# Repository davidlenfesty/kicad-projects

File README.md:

# kicad-projects

A repo for all my personal kicad PCB projects.

Included are some LED drivers for home automation purposes.

There isn't really anything special about this stuff.

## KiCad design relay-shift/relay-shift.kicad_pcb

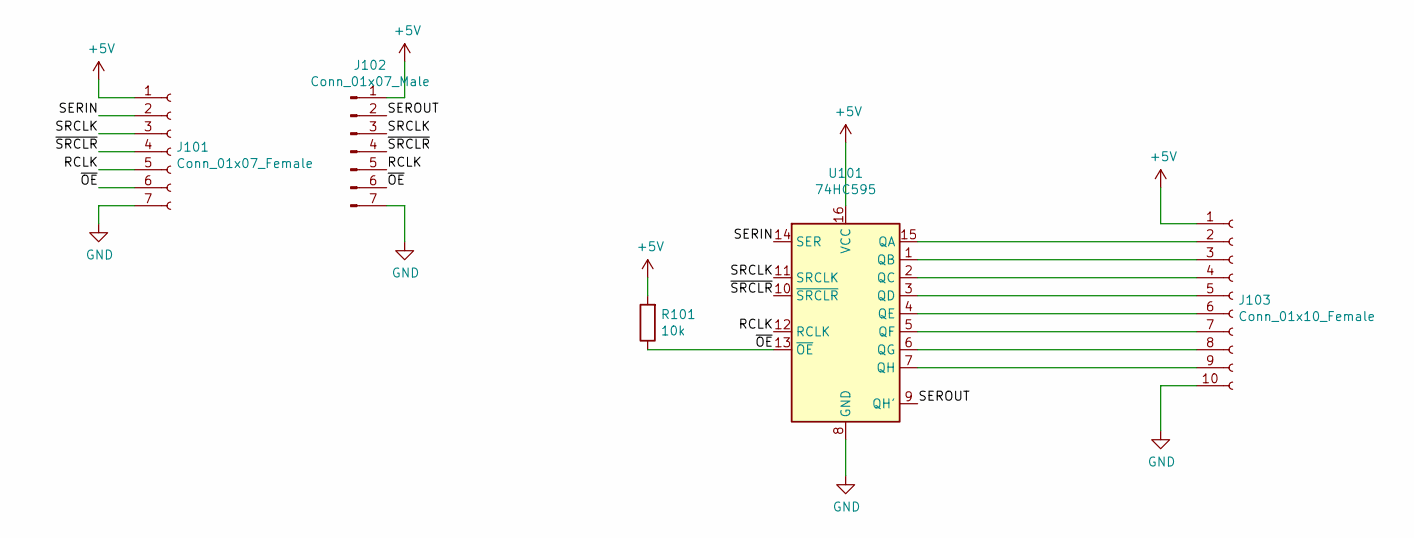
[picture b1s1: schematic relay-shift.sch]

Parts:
J101: Conn_01x07_Female; Molex_CLIK-Mate_502494-0870_1x08-1MP_P2.00mm_Horizontal
J102: Conn_01x07_Male; Molex_CLIK-Mate_502494-0870_1x08-1MP_P2.00mm_Horizontal
J103: Conn_01x10_Female; PinHeader_1x10_P2.54mm_Vertical
R101: 10k; R_0805_2012Metric
U101: 74HC595; SOIC-16W_7.5x10.3mm_P1.27mm

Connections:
+5V: J101.1, J102.1, J103.1, R101.2, U101.16 (VCC)
/RCLK: J101.5, J102.5, U101.12 (RCLK)
/SERIN: J101.2, U101.14 (SER)
/SEROUT: J102.2, U101.9 (QH')
/SRCLK: J101.3, J102.3, U101.11 (SRCLK)
/~OE: J101.6, J102.6, R101.1, U101.13 (~OE)
/~SRCLR: J101.4, J102.4, U101.10 (~SRCLR)
GND: J101.7, J102.7, J103.10, U101.8 (GND)
unnamed: J103.2, U101.15 (QA)
unnamed: J103.3, U101.1 (QB)
unnamed: J103.4, U101.2 (QC)
unnamed: J103.5, U101.3 (QD)
unnamed: J103.6, U101.4 (QE)
unnamed: J103.7, U101.5 (QF)
unnamed: J103.8, U101.6 (QG)
unnamed: J103.9, U101.7 (QH)

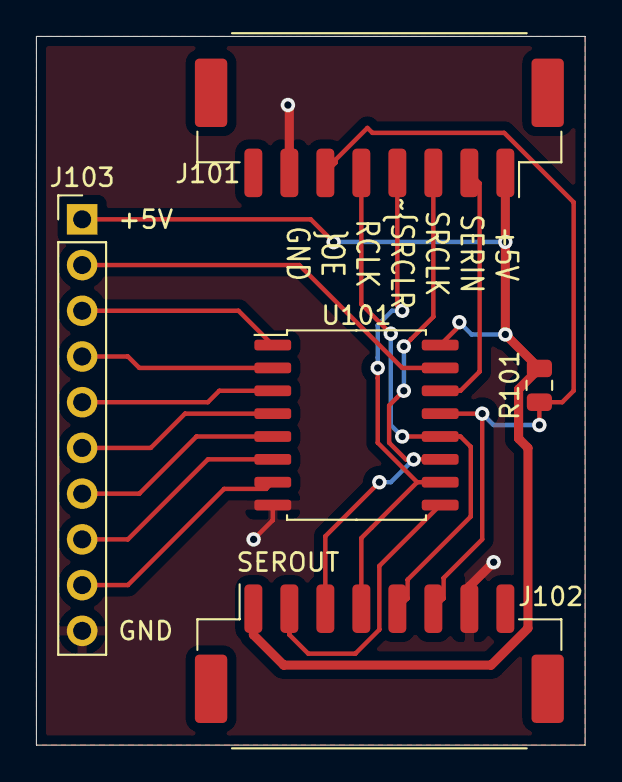
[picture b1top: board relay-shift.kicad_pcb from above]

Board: 2 copper layers, 30.5 x 39.4 mm, 5 parts (0 on the bottom side), 16 nets.

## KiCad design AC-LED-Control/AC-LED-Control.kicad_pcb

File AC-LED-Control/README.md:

# DO NOT USE THIS #

I made this board for a personal project.

Never use this.

I made this board using what I *think* were good tolerances.

Never use this.

I have not had the time to test this board.

Never use this.

This board is designed for AC.

Never use this.

Unless it's like 24VAC then that's okay I guess but I'm not responsible for it.

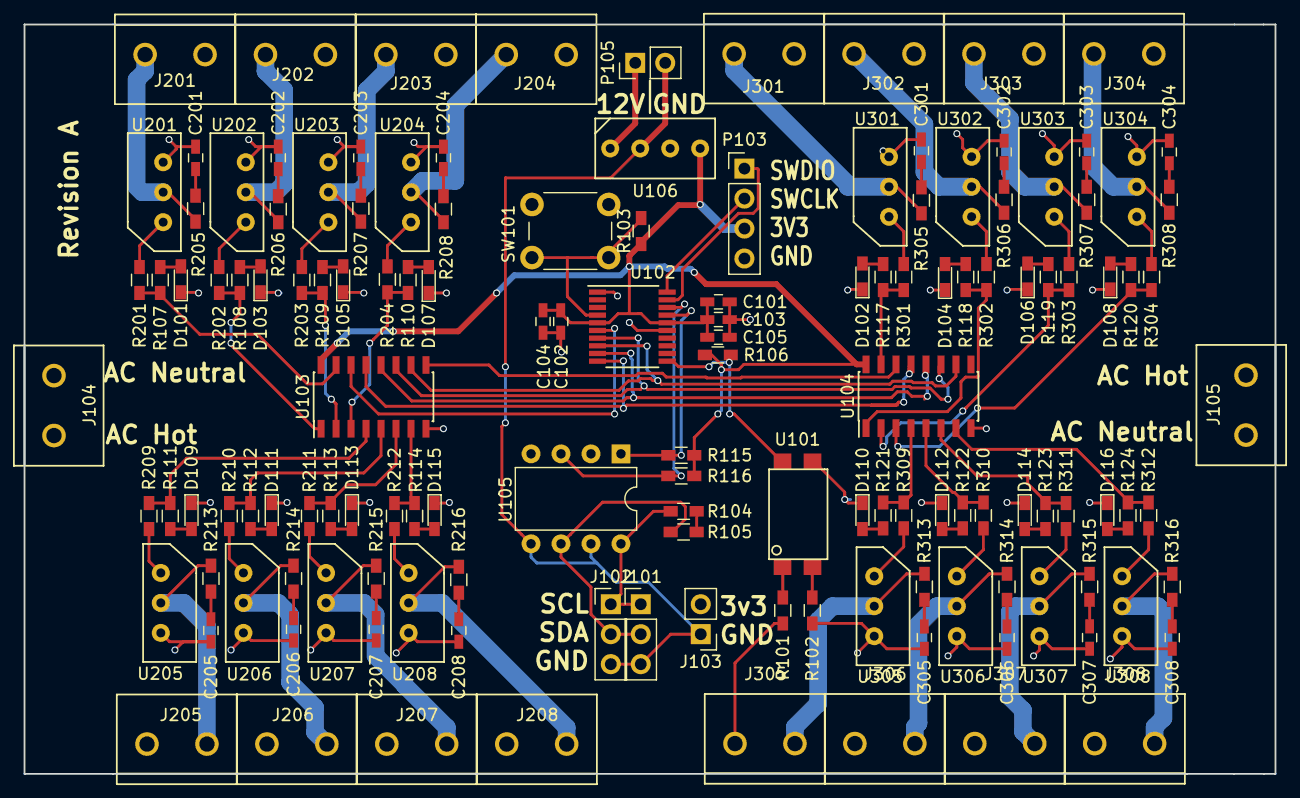
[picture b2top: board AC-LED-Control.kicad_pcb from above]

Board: 4 copper layers, 106.0 x 63.5 mm, 139 parts (0 on the bottom side), 103 nets.

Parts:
C101, C103: 100nF; C_0603_HandSoldering
C102: 10nF; C_0603_HandSoldering
C104: 1uF; C_0603_HandSoldering
C105: 4.7uF; C_0603_HandSoldering
C201, C202, C203, C204, C205, C206, C207, C208, C301, C302, C303, C304, C305, C306, C307, C308: 22n; C_0603_HandSoldering
D101, D102, D103, D104, D105, D106, D107, D108, D109, D110, D111, D112, D113, D114, D115, D116: LED; LED_0603_HandSoldering
J101, J102: Conn_01x03; Pin_Header_Straight_1x03_Pitch2.54mm
J103: Conn_01x02; Pin_Header_Straight_1x02_Pitch2.54mm
J104, J105, J201, J202, J203, J204, J205, J206, J207, J208, J301, J302, J303, J304, J305, J306, J307, J308: Conn_01x02; OSTTC022162
P103: CONN_01X04; Pin_Header_Straight_1x04_Pitch2.54mm
P105: CONN_01X02; Pin_Header_Straight_1x02_Pitch2.54mm
R101, R102, R103: 16K; R_0603_HandSoldering
R104, R105, R106: 2K; R_0603_HandSoldering
R107, R108, R109, R110, R111, R112, R113, R114, R117, R118, R119, R120, R121, R122, R123, R124: 160; R_0603_HandSoldering
R115, R116: 680; R_0603_HandSoldering
R201, R202, R203, R204, R209, R210, R211, R212, R301, R302, R303, R304, R309, R310, R311, R312: 100; R_0603_HandSoldering
R205, R206, R207, R208, R213, R214, R215, R216, R305, R306, R307, R308, R313, R314, R315, R316: 56; R_0603_HandSoldering
SW101: SW_PUSH; SW_PUSH_6mm_h5mm
U101: FOD814-D; OnSemi_PDIP4
U102: STM32F030F4P6; TSSOP-20_4.4x6.5mm_Pitch0.65mm
U103, U104: 74HC595; SOIC-16_3.9x9.9mm_Pitch1.27mm
U105: LTV-827; DIP-8_W7.62mm
U106: IE1203S; SIP-4
U201, U202, U203, U204, U205, U206, U207, U208, U301, U302, U303, U304, U305, U306, U307, U308: TRIAC; TO-202-3-Vertical

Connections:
+3V3: C101.1, C102.1, C103.1, C104.1, C105.1, P103.3, R103.1, R106.1, R115.2, R116.2, U102.5, U102.16, U103.16, U104.16, U106.4
/3v3_ISO: R104.1, R105.1
/+12V_IN: P105.1, U106.1
/CHAN0: R107.2, R201.2, U103.15
/CHAN1: R108.2, R202.2, U103.1
/CHAN2: R109.2, R203.2, U103.2
/CHAN3: R110.2, R204.2, U103.3
/CHAN4: R111.2, R209.2, U103.4
/CHAN5: R112.2, R210.2, U103.5
/CHAN6: R113.2, R211.2, U103.6
/CHAN7: R114.2, R212.2, U103.7
/CHAN8: R117.2, R301.2, U104.15
/CHAN9: R118.2, R302.2, U104.1
/CHAN10: R119.2, R303.2, U104.2
/CHAN11: R120.2, R304.2, U104.3
/CHAN12: R121.2, R309.2, U104.4
/CHAN13: R122.2, R310.2, U104.5
/CHAN14: R123.2, R311.2, U104.6
/CHAN15: R124.2, R312.2, U104.7
/GND_IN: J101.3, J102.3, J103.1, P105.2, U105.5, U105.7, U106.2
/I2C_SCL: J101.1, J102.1, R104.2, U105.8
/I2C_SDA: J101.2, J102.2, R105.2, U105.6
/Output-BankA/AC_LOAD-A: J201.1, R205.1, U201.2
/Output-BankA/AC_LOAD-B: J202.1, R206.1, U202.2
/Output-BankA/AC_LOAD-C: J203.1, R207.1, U203.2
/Output-BankA/AC_LOAD-D: J204.1, R208.1, U204.2
/Output-BankA/AC_LOAD-E: J205.1, R213.1, U205.2
/Output-BankA/AC_LOAD-F: J206.1, R214.1, U206.2
/Output-BankA/AC_LOAD-G: J207.1, R215.1, U207.2
/Output-BankA/AC_LOAD-H: J208.1, R216.1, U208.2
/Output-BankB/AC_LOAD-A: J301.1, R305.1, U301.2
/Output-BankB/AC_LOAD-B: J302.1, R306.1, U302.2
/Output-BankB/AC_LOAD-C: J303.1, R307.1, U303.2
/Output-BankB/AC_LOAD-D: J304.1, R308.1, U304.2
/Output-BankB/AC_LOAD-E: J305.1, R313.1, U305.2
/Output-BankB/AC_LOAD-F: J306.1, R314.1, U306.2
/Output-BankB/AC_LOAD-G: J307.1, R315.1, U307.2
/Output-BankB/AC_LOAD-H: J308.1, R316.1, U308.2
/STM_SCL: R115.1, U102.17, U105.1
/STM_SDA: R116.1, U102.18, U105.3
/STM_SWCLK: P103.2, U102.20
/STM_SWDIO: P103.1, U102.19
/STM_~RST: R103.2, SW101.2, U102.4
/Shift_RCLK: U102.9, U103.12, U104.12
/Shift_SER: U102.6, U103.14
/Shift_SRCLK: U102.7, U103.11, U104.11
/Shift_~OE: U102.10, U103.13, U104.13
/Shift_~SRCLR: U102.8, U103.10, U104.10
/ZERO_CROSS: R106.2, U101.4, U102.11
AC-H: J104.1, J105.1, J201.2, J202.2, J203.2, J204.2, J205.2, J206.2, J207.2, J208.2, J301.2, J302.2, J303.2, J304.2, J305.2, J306.2, J307.2, J308.2, R101.2
AC-N: C201.1, C202.1, C203.1, C204.1, C205.1, C206.1, C207.1, C208.1, C301.1, C302.1, C303.1, C304.1, C305.1, C306.1, C307.1, C308.1, J104.2, J105.2, R102.2, U201.1, U202.1, U203.1, U204.1, U205.1, U206.1, U207.1, U208.1, U301.1, U302.1, U303.1, U304.1, U305.1, U306.1, U307.1, U308.1
GND: C101.2, C102.2, C103.2, C104.2, C105.2, D101.1, D102.1, D103.1, D104.1, D105.1, D106.1, D107.1, D108.1, D109.1, D110.1, D111.1, D112.1, D113.1, D114.1, D115.1, D116.1, P103.4, SW101.1, U101.3, U102.1, U102.15, U103.8, U104.8, U105.2, U105.4, U106.3
unnamed: C201.2, R205.2
unnamed: C202.2, R206.2
unnamed: C203.2, R207.2
unnamed: C204.2, R208.2
unnamed: C205.2, R213.2
unnamed: C206.2, R214.2
unnamed: C207.2, R215.2
unnamed: C208.2, R216.2
unnamed: C301.2, R305.2
unnamed: C302.2, R306.2
unnamed: C303.2, R307.2
unnamed: C304.2, R308.2
unnamed: C305.2, R313.2
unnamed: C306.2, R314.2
unnamed: C307.2, R315.2
unnamed: C308.2, R316.2
unnamed: D101.2, R107.1
unnamed: D102.2, R117.1
unnamed: D103.2, R108.1
unnamed: D104.2, R118.1
unnamed: D105.2, R109.1
unnamed: D106.2, R119.1
unnamed: D107.2, R110.1
unnamed: D108.2, R120.1
unnamed: D109.2, R111.1
unnamed: D110.2, R121.1
unnamed: D111.2, R112.1
unnamed: D112.2, R122.1
unnamed: D113.2, R113.1
unnamed: D114.2, R123.1
unnamed: D115.2, R114.1
unnamed: D116.2, R124.1
unnamed: R101.1, U101.1
unnamed: R102.1, U101.2
unnamed: R201.1, U201.3
unnamed: R202.1, U202.3
unnamed: R203.1, U203.3
unnamed: R204.1, U204.3
unnamed: R209.1, U205.3
unnamed: R210.1, U206.3
unnamed: R211.1, U207.3
unnamed: R212.1, U208.3
unnamed: R301.1, U301.3
unnamed: R302.1, U302.3
unnamed: R303.1, U303.3
unnamed: R304.1, U304.3
unnamed: R309.1, U305.3
unnamed: R310.1, U306.3
unnamed: R311.1, U307.3
unnamed: R312.1, U308.3
unnamed: U103.9, U104.14

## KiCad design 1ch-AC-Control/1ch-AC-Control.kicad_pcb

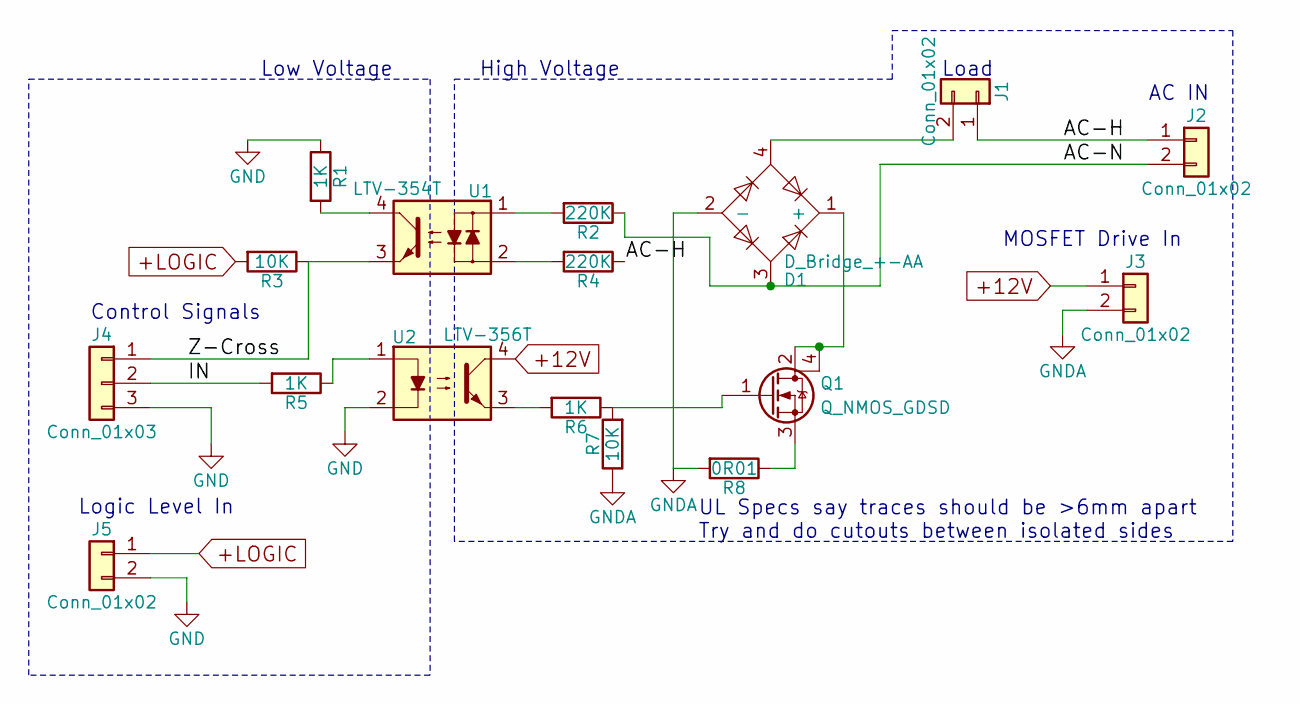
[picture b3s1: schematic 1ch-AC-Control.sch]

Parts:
D1: D_Bridge_+-AA; SOPA-4
J1, J2, J3, J5: Conn_01x02; Pin_Header_Straight_1x02_Pitch2.54mm
J4: Conn_01x03; Pin_Header_Straight_1x03_Pitch2.54mm
Q1: Q_NMOS_GDSD; SOT-223
R1, R5, R6: 1K; R_0805_HandSoldering
R2, R4: 220K; R_0805_HandSoldering
R3, R7: 10K; R_0805_HandSoldering
R8: 0R01; R_0805_HandSoldering
U1: LTV-354T; SO-4_4.4x3.6mm_Pitch2.54mm
U2: LTV-356T; SO-4_4.4x3.6mm_Pitch2.54mm

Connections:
+12V: J3.1, U2.4
+LOGIC: J5.1, R3.2
/AC-H: J1.1, J2.1, R4.1
/AC-N: D1.3, J2.2, R2.1
/IN: J4.2, R5.2
/Z-Cross: J4.1, R3.1, U1.3
GND: J4.3, J5.2, R1.1, U2.2
GNDA: D1.2 (-), J3.2, R7.1, R8.2
unnamed: D1.1 (+), Q1.2 (D), Q1.4 (D)
unnamed: D1.4, J1.2
unnamed: Q1.1 (G), R6.1, R7.2
unnamed: Q1.3 (S), R8.1
unnamed: R1.2, U1.4
unnamed: R2.2, U1.1
unnamed: R4.2, U1.2
unnamed: R5.1, U2.1
unnamed: R6.2, U2.3

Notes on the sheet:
AC IN
Load
Logic Level In
Control Signals
Low Voltage
High Voltage
MOSFET Drive In
UL Specs say traces should be >6mm apart Try and do cutouts between isolated sides

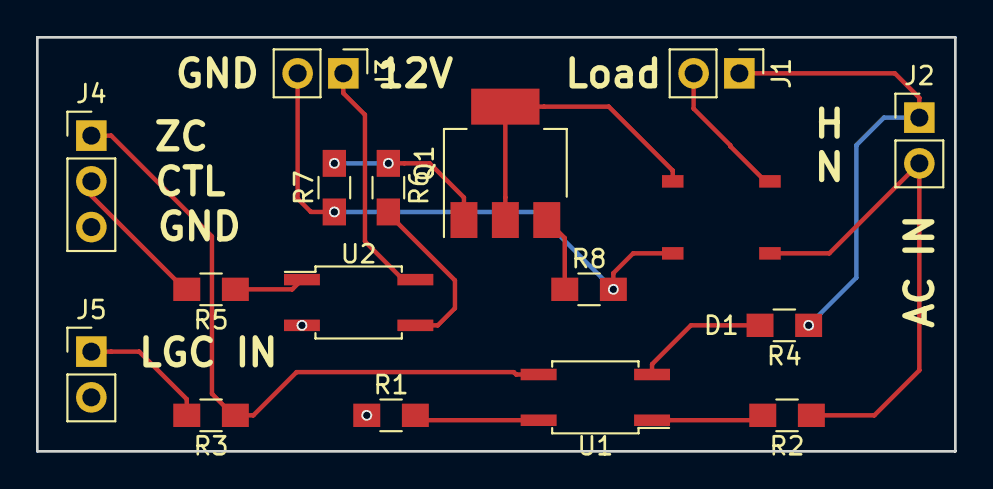
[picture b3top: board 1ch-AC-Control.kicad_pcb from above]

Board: 2 copper layers, 51.0 x 23.0 mm, 17 parts (0 on the bottom side), 17 nets.

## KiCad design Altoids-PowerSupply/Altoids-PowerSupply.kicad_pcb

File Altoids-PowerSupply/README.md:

# Altoids Power Supply README #

## Intro ##

I saw a tin of altoids at the grocery store the other day. I decided that if I was going to get into electronics I better do at least one project using an altoids tin. Also I really don't have a good power supply (an atx supply with a mess of wires doesn't count), so I figured I'd make a portable power supply with some common voltage rails.

Thus, this project was born.

## Main Goals ##

Battery powered PSU with common voltage rails (for me at least).

Must have features:
- 5v rail.
- 3v3 rail.
- Battery and a way to convienently charge it (USB)

Wants:
- 12V rail. (I don't know why)
- 5V USB output (as a phone charger)

I also wanted to learn about switch mode power supplies, so I used two MC34063s, one for the 5V and one for the 12V. (EEVBlog's tutorial was INCREDIBLY useful). 3v3 works better as a linear supply because you don't have to drop too much voltage.

Li-ion charging is also a new thing for me, so this will be a learning curve.

## Rev A ##

Finished layout, design files are done.

Max current is:
- 300mA for 5V and 3v3
- 100mA for 12V

### Issues ###

- No silkscreen labelling for what's what.
- Unsure if it actually works (haven't received the board/put it together yet)
- The 'cutoff' transistor should really be controlled by an NPN switch, the circuit should default off.
- Probably should have chosen a different diode (especially for 12v) with higher current capabilities
- Component choices are hit and miss, smaller, cheaper components could have been selected (I went with most of my current choices just to make ordering and layout simpler and more consistent).
- Double sided load. Ideally all the components (especially surface mount) should be on one side. This comes down to component selection mostly. Not sure how much extra space I have (or could have).
- Minimum size you can get of 330uF caps is 6.3mm diam, need to change out this footprint.
- Really I should select the components and download footprints from digikey
- switch will need to be bodged in

## Rev B ##

I'm starting this right now with the silkscreen corrections, just so I don't forget them again.

### TODO ###

- make the cutoff transistor default off.
- fix other issues that pop up.

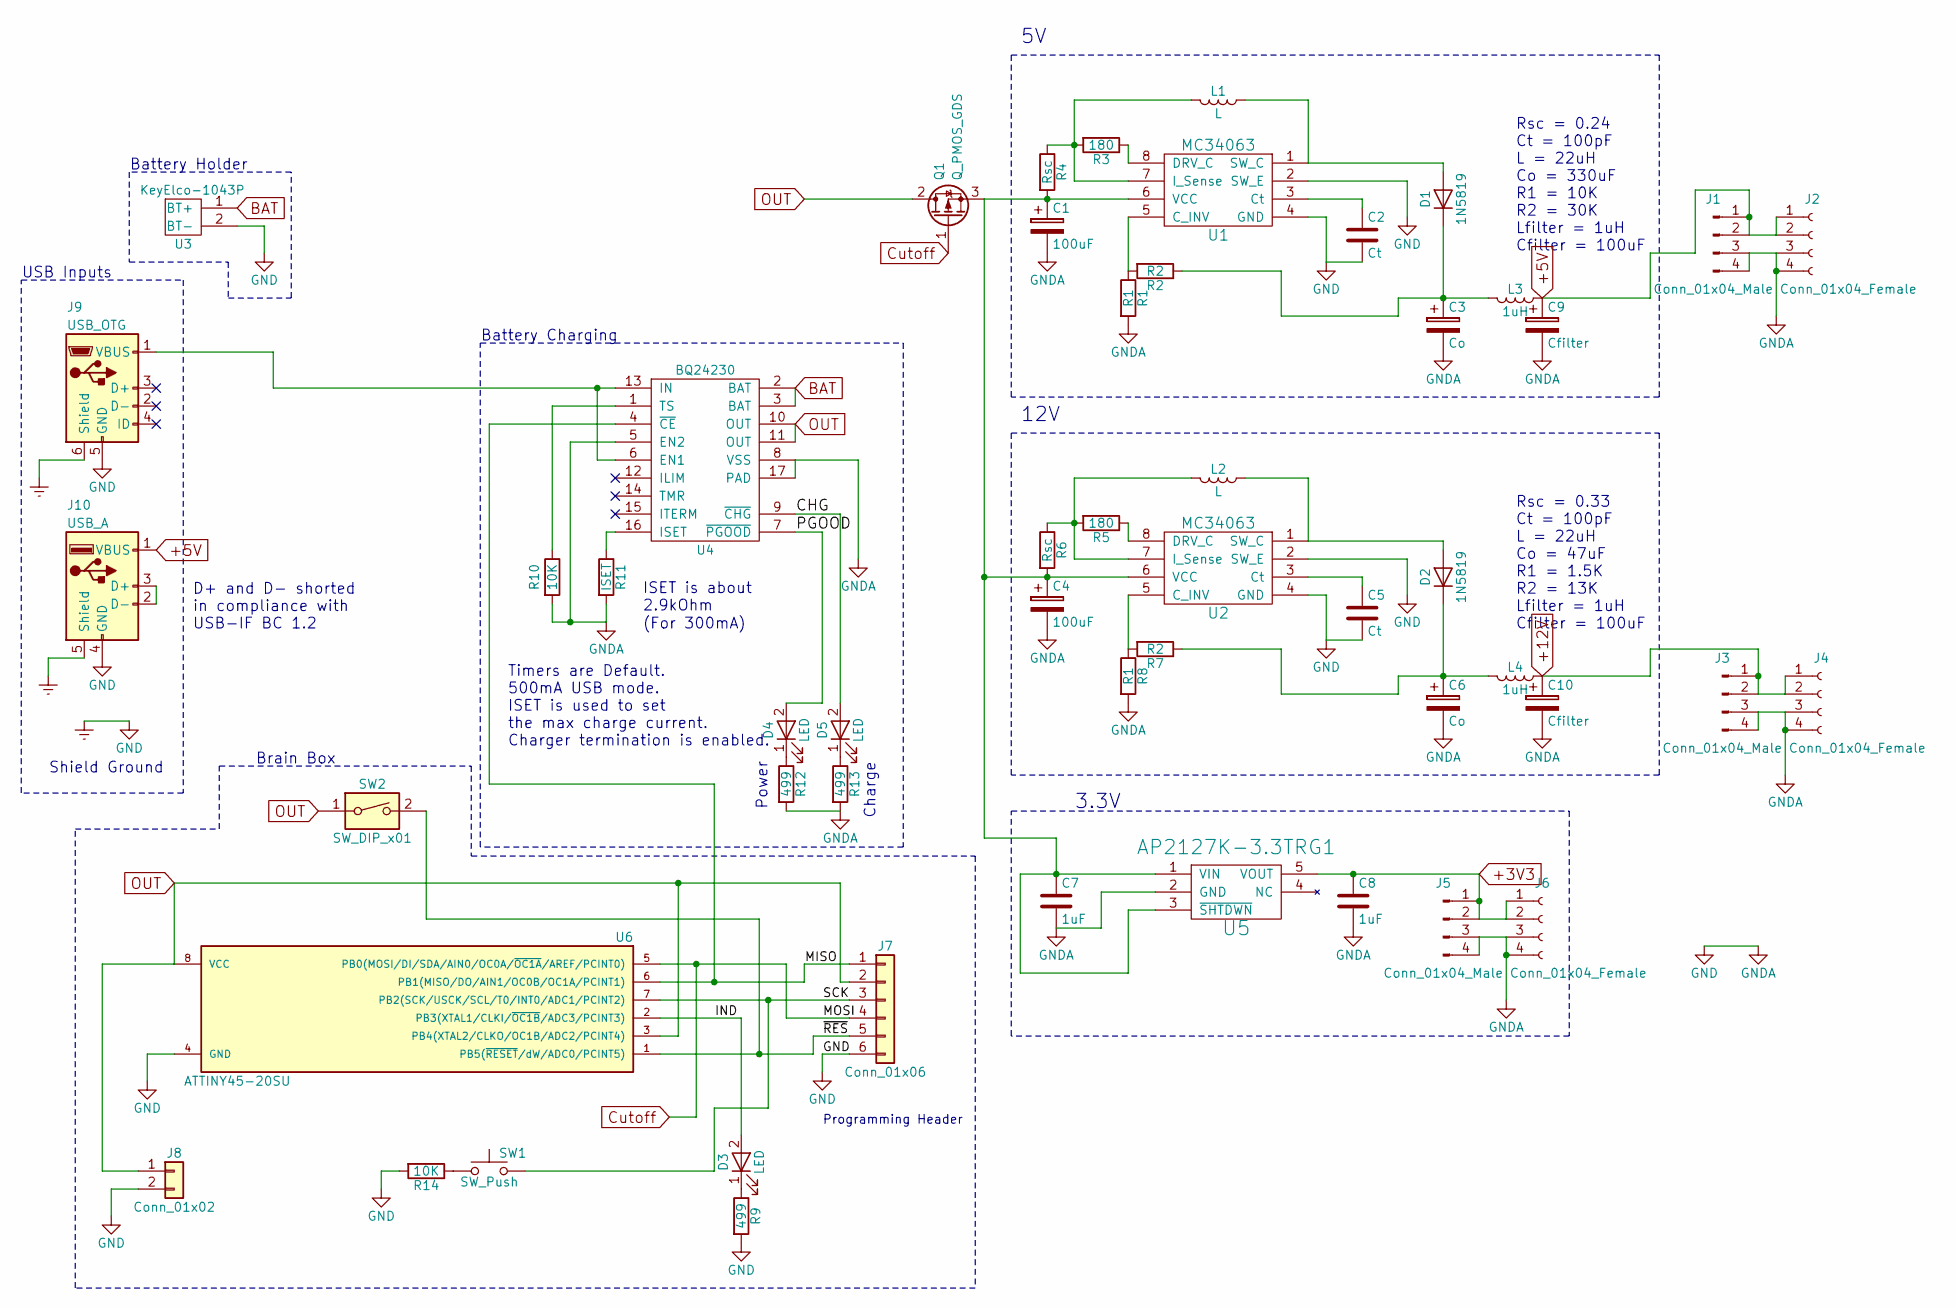
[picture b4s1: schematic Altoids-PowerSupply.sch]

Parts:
C1, C4: 100uF; CP_Elec_5x5.3
C2, C5: Ct; C_0805_HandSoldering
C3, C6: Co; CP_Elec_5x5.3
C7, C8: 1uF; C_0805_HandSoldering
C9, C10: Cfilter; CP_Elec_5x5.3
D1, D2: 1N5819; D_0805
D3, D4, D5: LED; LED_0805_HandSoldering
J1, J3, J5: Conn_01x04_Male; Pin_Header_Straight_1x04_Pitch2.54mm
J2, J4, J6: Conn_01x04_Female; Socket_Strip_Straight_1x04_Pitch2.54mm
J7: Conn_01x06; Pin_Header_Straight_2x03_Pitch2.54mm
J8: Conn_01x02; Pin_Header_Straight_1x02_Pitch2.54mm
J9: USB_OTG; USB_Micro-B
J10: USB_A
L1, L2: L; L_Radial_D9.5mm_P5.00mm_Fastron_07HVP
L3, L4: 1uH; L_Axial_L12.0mm_D5.0mm_P5.08mm_Vertical_Fastron_MISC
Q1: Q_PMOS_GDS; TO-263-2
R1, R8: R1; R_0805_HandSoldering
R2, R7: R2; R_0805_HandSoldering
R3, R5: 180; R_0805_HandSoldering
R4, R6: Rsc; R_1206_HandSoldering
R9, R12, R13: 499; R_0805_HandSoldering
R10, R14: 10K; R_0805_HandSoldering
R11: ISET; R_0805_HandSoldering
SW1: SW_Push; SW_SPST_PTS810
SW2: SW_DIP_x01; SW_DIP_x1_W5.08mm_Slide_Copal_CHS-A
U1, U2: MC34063; SOIC-8_3.9x4.9mm_Pitch1.27mm
U3: KeyElco-1043P
U4: BQ24230; QFN-16-1EP_3x3mm_Pitch0.5mm_ThermalVias
U5: AP2127K-3.3TRG1; SOT-23-5
U6: ATTINY45-20SU; SOIC-8_3.9x4.9mm_Pitch1.27mm

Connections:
+3V3: C8.1, J5.1, J5.2, J6.1, J6.2, U5.5 (VOUT)
+5V: C9.1, J1.1, J1.2, J2.1, J2.2, J10.1 (VBUS), L3.1
+12V: C10.1, J3.1, J3.2, J4.1, J4.2, L4.1
/CHG: D5.2 (A), U4.9 (~CHG)
/IND: D3.2 (A), U6.2 (PB3(XTAL1/CLKI/~OC1B~/ADC3/PCINT3))
/MISO: J7.1, U4.4 (~CE), U6.6 (PB1(MISO/DO/AIN1/OC0B/OC1A/PCINT1))
/PGOOD: D4.2 (A), U4.7 (~PGOOD)
/SCK: J7.3, SW1.2, U6.7 (PB2(SCK/USCK/SCL/T0/INT0/ADC1/PCINT2))
/~RES: J7.5, SW2.2, U6.1 (PB5(~RESET~/dW/ADC0/PCINT5))
BAT: U3.1 (BT+), U4.2 (BAT), U4.3 (BAT)
Cutoff: J7.4, Q1.1 (G), U6.5 (PB0(MOSI/DI/SDA/AIN0/OC0A/~OC1A~/AREF/P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)
Earth: C1.2, C2.2, C3.2, C4.2, C5.2, C6.2, C7.2, C8.2, C9.2, C10.2, J1.3, J1.4, J2.3, J2.4, J3.3, J3.4, J4.3, J4.4, J5.3, J5.4, J6.3, J6.4, J7.6, J8.2, J9.5 (GND), J9.6 (Shield), J10.4 (GND), J10.5 (Shield), R1.2, R8.2, R9.2, R10.2, R11.2, R12.2, R13.2, R14.2, U1.2 (SW_E), U1.4 (GND), U2.2 (SW_E), U2.4 (GND), U3.2 (BT-), U4.5 (EN2), U4.8 (VSS), U4.17 (PAD), U5.2 (GND), U6.4 (GND)
unnamed: C1.1, C4.1, C7.1, Q1.3 (S), R4.2, R6.2, U1.6 (VCC), U2.6 (VCC), U5.1 (VIN), U5.3 (~SHTDWN)
unnamed: C2.1, U1.3 (Ct)
unnamed: C3.1, D1.1 (K), L3.2, R2.1
unnamed: C5.1, U2.3 (Ct)
unnamed: C6.1, D2.1 (K), L4.2, R7.1
unnamed: D1.2 (A), L1.1, U1.1 (SW_C)
unnamed: D2.2 (A), L2.1, U2.1 (SW_C)
unnamed: D3.1 (K), R9.1
unnamed: D4.1 (K), R12.1
unnamed: D5.1 (K), R13.1
unnamed: J9.1 (VBUS), U4.6 (EN1), U4.13 (IN)
unnamed: J10.2 (D-), J10.3 (D+)
unnamed: L1.2, R3.2, R4.1, U1.7 (I_Sense)
unnamed: L2.2, R5.2, R6.1, U2.7 (I_Sense)
unnamed: R1.1, R2.2, U1.5 (C_INV)
unnamed: R3.1, U1.8 (DRV_C)
unnamed: R5.1, U2.8 (DRV_C)
unnamed: R7.2, R8.1, U2.5 (C_INV)
unnamed: R10.1, U4.1 (TS)
unnamed: R11.1, U4.16 (ISET)
unnamed: R14.1, SW1.1
OUT: J7.2, J8.1, Q1.2 (D), SW2.1, U4.10 (OUT), U4.11 (OUT), U6.3 (PB4(XTAL2/CLKO/OC1B/ADC2/PCINT4)), U6.8 (VCC)

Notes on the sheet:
Rsc = 0.24 Ct = 100pF L = 22uH Co = 330uF R1 = 10K R2 = 30K Lfilter = 1uH Cfilter = 100uF
Rsc = 0.33 Ct = 100pF L = 22uH Co = 47uF R1 = 1.5K R2 = 13K Lfilter = 1uH Cfilter = 100uF
12V
3.3V
Programming Header
Shield Ground
Timers are Default. 500mA USB mode. ISET is used to set the max charge current. Charger termination is enabled.
Charge
Power
USB Inputs
Battery Holder
Brain Box
Battery Charging
D+ and D- shorted in compliance with USB-IF BC 1.2
ISET is about 2.9kOhm
(For 300mA)

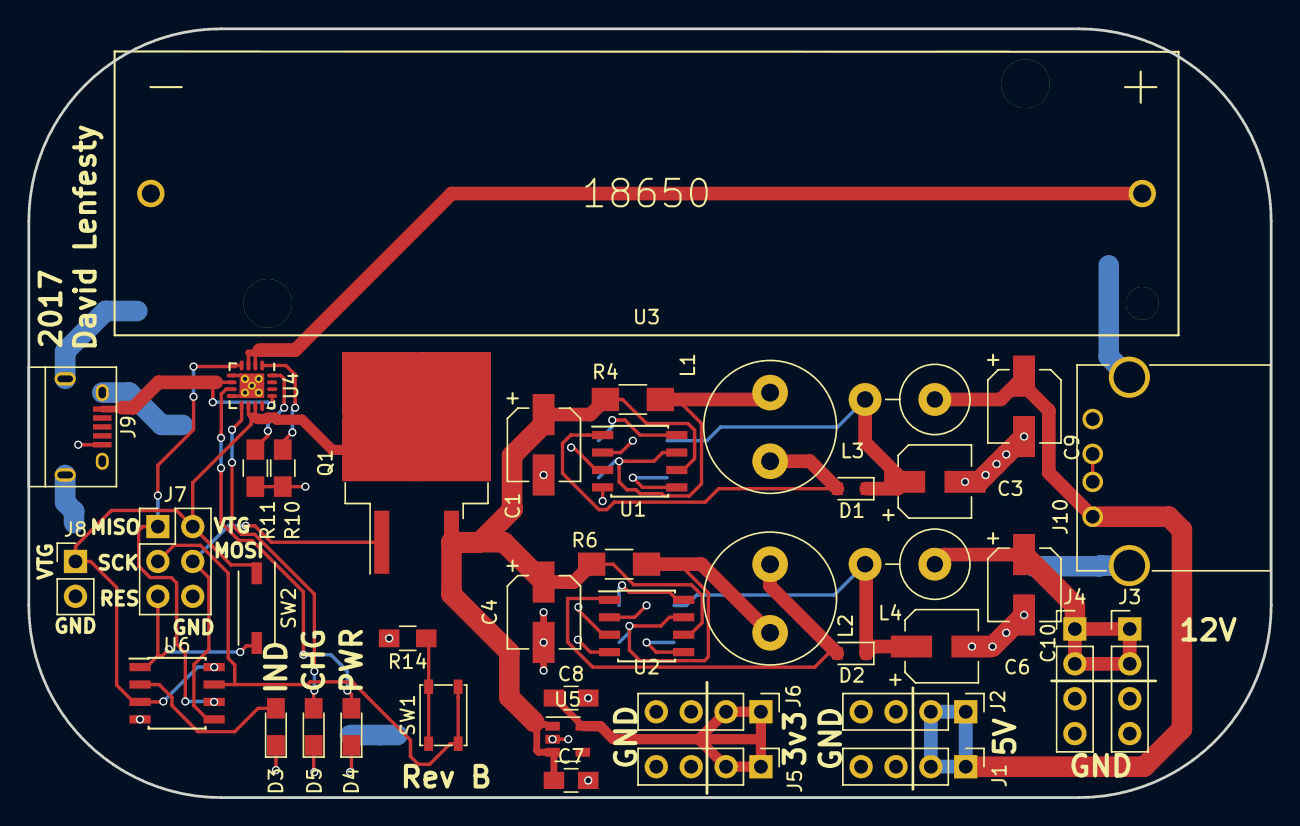
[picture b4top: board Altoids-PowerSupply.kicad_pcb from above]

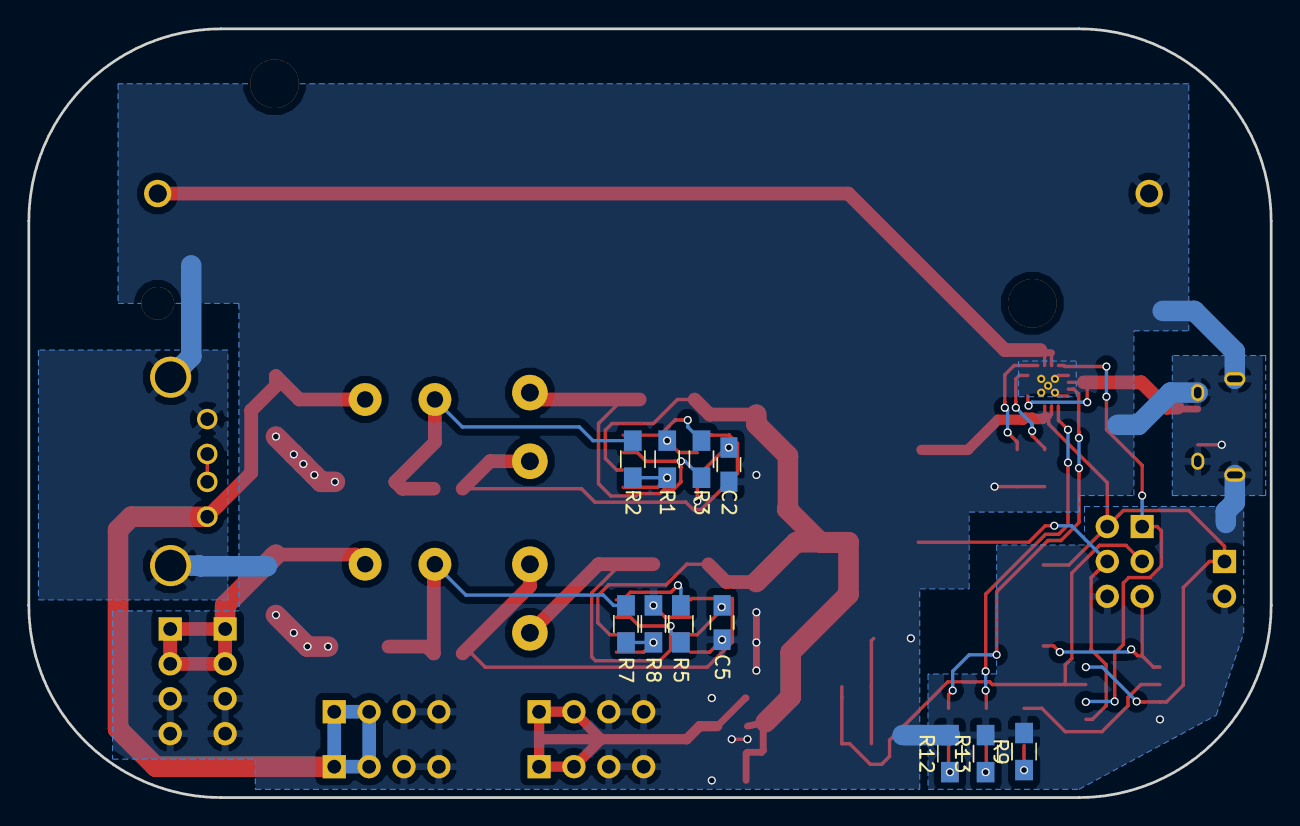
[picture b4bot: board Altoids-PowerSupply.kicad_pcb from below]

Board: 2 copper layers, 90.5 x 56.0 mm, 52 parts (11 on the bottom side), 34 nets.

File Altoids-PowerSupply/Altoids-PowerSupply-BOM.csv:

"Id";"Designator";"Package";"Quantity";"Designation";"Supplier and ref";
1;"U2,U1";"SOIC-8_3.9x4.9mm_Pitch1.27mm";2;"MC34063";;;
2;"C1,C4";"CP_Elec_5x5.3";2;"100uF";;;
3;"C2,C5";"C_0805_HandSoldering";2;"Ct";;;
4;"C3,C6";"CP_Elec_5x5.3";2;"Co";;;
5;"C7,C8";"C_0805_HandSoldering";2;"1uF";;;
6;"C9,C10";"CP_Elec_5x5.3";2;"Cfilter";;;
7;"D1,D2";"D_0805";2;"1N5819";;;
8;"D3,D4,D5";"LED_0805_HandSoldering";3;"LED";;;
9;"J1,J3,J5";"Pin_Header_Straight_1x04_Pitch2.54mm";3;"Conn_01x04_Male";;;
10;"J8";"Pin_Header_Straight_1x02_Pitch2.54mm";1;"Conn_01x02";;;
11;"J9";"USB_Micro-B";1;"USB_OTG";;;
12;"J10";"USB_A";1;"USB_A";;;
13;"L1,L2";"L_Radial_D9.5mm_P5.00mm_Fastron_07HVP";2;"L";;;
14;"L3,L4";"L_Axial_L12.0mm_D5.0mm_P5.08mm_Vertical_Fastron_MISC";2;"1uH";;;
15;"Q1";"TO-263-2";1;"Q_PMOS_GDS";;;
16;"R1,R8";"R_0805_HandSoldering";2;"R1";;;
17;"R2,R7";"R_0805_HandSoldering";2;"R2";;;
18;"R3,R5";"R_0805_HandSoldering";2;"180";;;
19;"R4,R6";"R_1206_HandSoldering";2;"Rsc";;;
20;"R9,R12,R13";"R_0805_HandSoldering";3;"499";;;
21;"R10,R14";"R_0805_HandSoldering";2;"10K";;;
22;"R11";"R_0805_HandSoldering";1;"ISET";;;
23;"U3";"KeyElco-1043P";1;"KeyElco-1043P";;;
24;"U4";"QFN-16-1EP_3x3mm_Pitch0.5mm_ThermalVias";1;"BQ24230";;;
25;"U5";"SOT-23-5";1;"AP2127K-3.3TRG1";;;
26;"U6";"SOIC-8_3.9x4.9mm_Pitch1.27mm";1;"ATTINY45-20SU";;;
27;"J2,J4,J6";"Socket_Strip_Straight_1x04_Pitch2.54mm";3;"Conn_01x04_Female";;;
28;"J7";"Pin_Header_Straight_2x03_Pitch2.54mm";1;"Conn_01x06";;;
29;"SW1";"SW_SPST_PTS810";1;"SW_Push";;;
30;"SW2";"SW_DIP_x1_W5.08mm_Slide_Copal_CHS-A";1;"SW_DIP_x01";;;

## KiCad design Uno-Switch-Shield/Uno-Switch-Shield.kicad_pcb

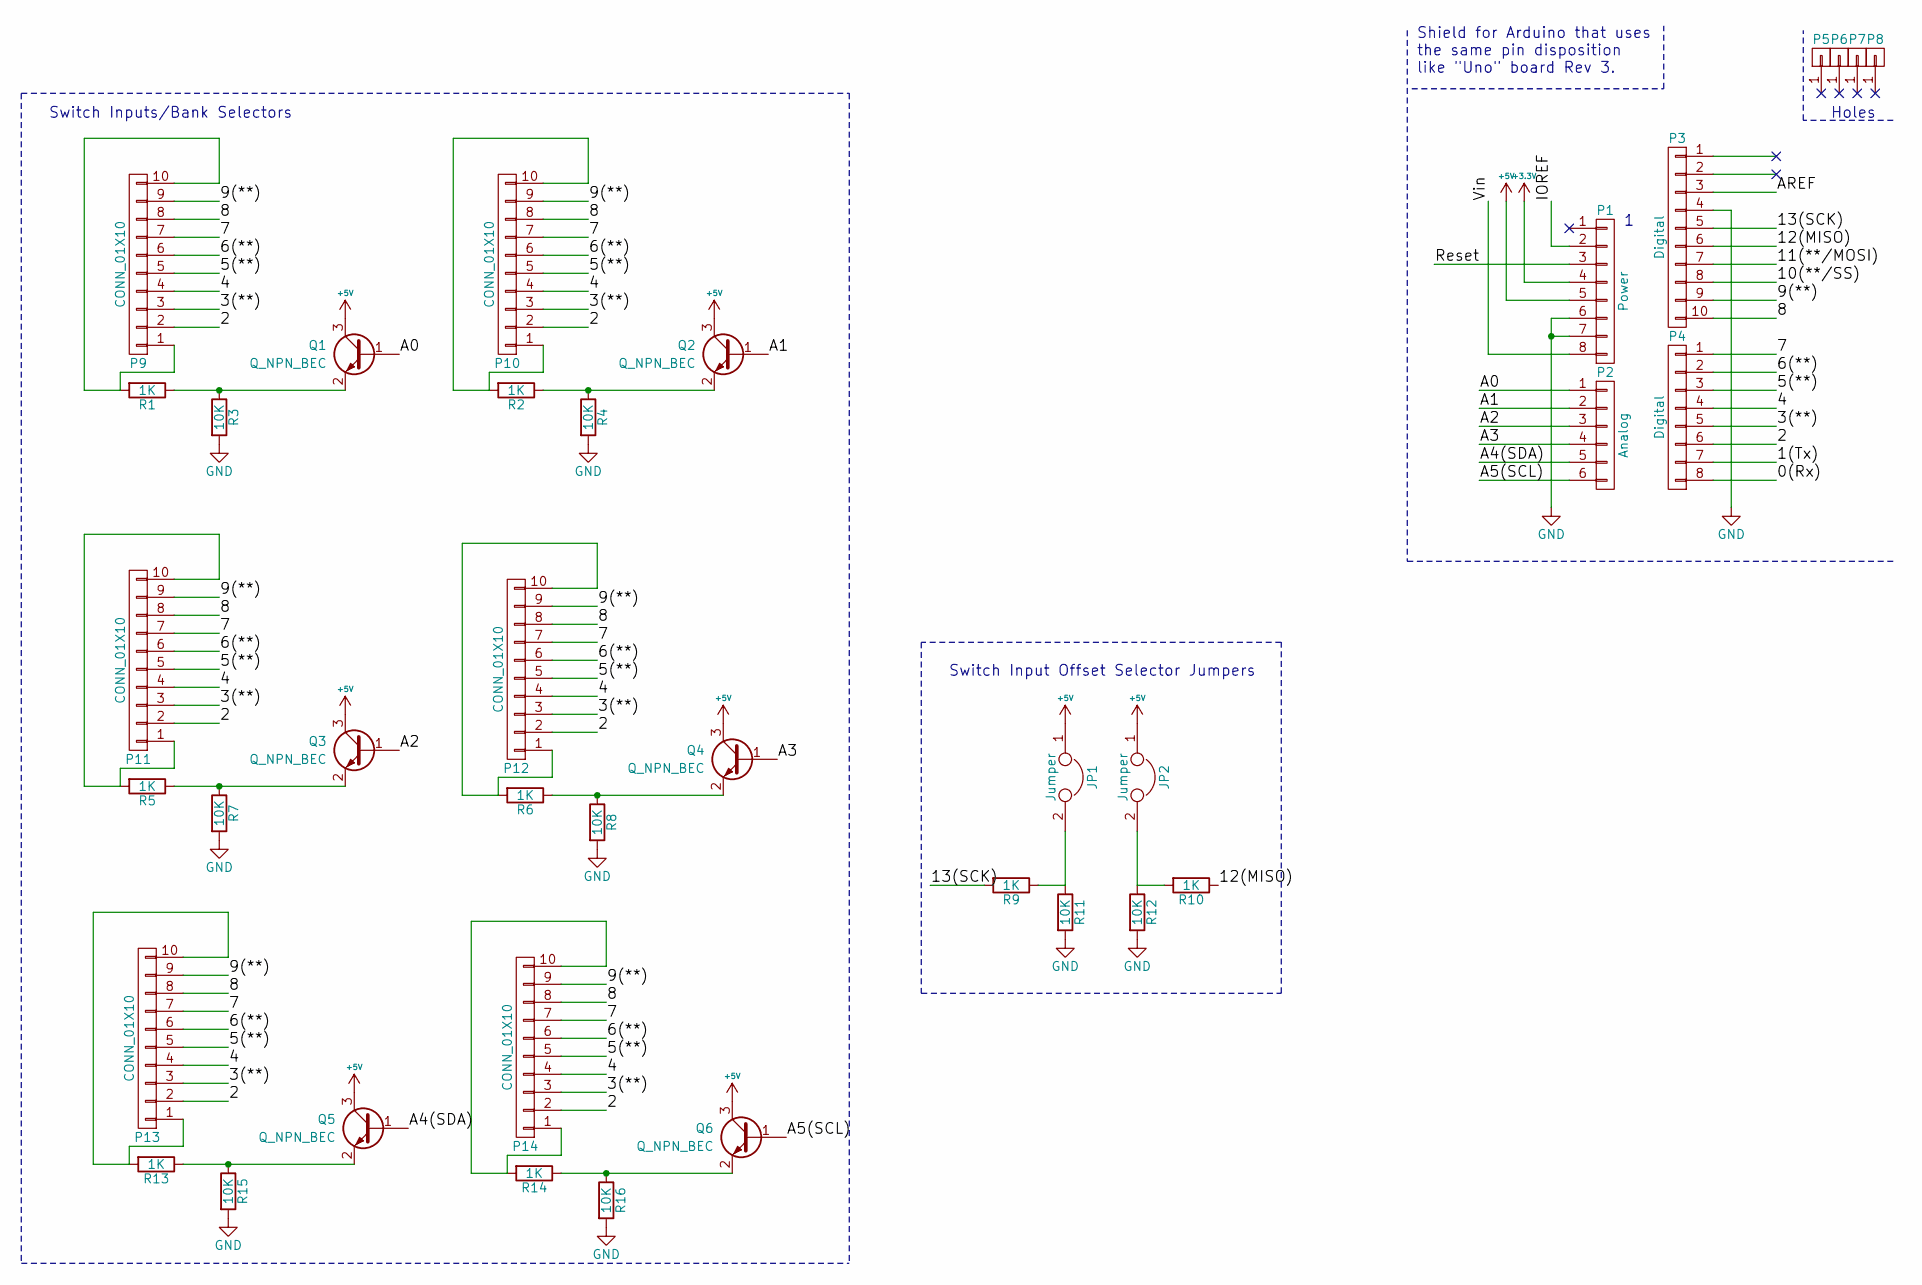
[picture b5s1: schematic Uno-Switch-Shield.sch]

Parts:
JP1, JP2: Jumper; Jumper_SMD
P1: Power; Socket_Strip_Arduino_1x08
P2: Analog; Socket_Strip_Arduino_1x06
P3: Digital; Socket_Strip_Arduino_1x10
P4: Digital; Socket_Strip_Arduino_1x08
P5, P6, P7, P8: CONN_01X01; Arduino_1pin
P9, P10, P11, P12, P13, P14: CONN_01X10; Socket_Strip_Straight_1x10_Pitch2.54mm
Q1, Q2, Q3, Q4, Q5, Q6: Q_NPN_BEC; SOT-23
R1, R2, R5, R6, R9, R10, R13, R14: 1K; R_0805
R3, R4, R7, R8, R11, R12, R15, R16: 10K; R_0805

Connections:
+3V3: P1.4
+5V: JP1.1, JP2.1, P1.5, Q1.3 (C), Q2.3 (C), Q3.3 (C), Q4.3 (C), Q5.3 (C), Q6.3 (C)
/0(Rx): P4.8
/1(Tx): P4.7
/2: P4.6, P9.2, P10.2, P11.2, P12.2, P13.2, P14.2
/3(**): P4.5, P9.3, P10.3, P11.3, P12.3, P13.3, P14.3
/4: P4.4, P9.4, P10.4, P11.4, P12.4, P13.4, P14.4
/5(**): P4.3, P9.5, P10.5, P11.5, P12.5, P13.5, P14.5
/6(**): P4.2, P9.6, P10.6, P11.6, P12.6, P13.6, P14.6
/7: P4.1, P9.7, P10.7, P11.7, P12.7, P13.7, P14.7
/8: P3.10, P9.8, P10.8, P11.8, P12.8, P13.8, P14.8
/9(**): P3.9, P9.9, P10.9, P11.9, P12.9, P13.9, P14.9
/10(**/SS): P3.8
/11(**/MOSI): P3.7
/12(MISO): P3.6, R10.1
/13(SCK): P3.5, R9.2
/A0: P2.1, Q1.1 (B)
/A1: P2.2, Q2.1 (B)
/A2: P2.3, Q3.1 (B)
/A3: P2.4, Q4.1 (B)
/A4(SDA): P2.5, Q5.1 (B)
/A5(SCL): P2.6, Q6.1 (B)
/AREF: P3.3
/IOREF: P1.2
/Reset: P1.3
/Vin: P1.8
GND: P1.6, P1.7, P3.4, R3.2, R4.2, R7.2, R8.2, R11.2, R12.2, R15.2, R16.2
unnamed: JP1.2, R9.1, R11.1
unnamed: JP2.2, R10.2, R12.1
unnamed: P9.1, P9.10, R1.2
unnamed: P10.1, P10.10, R2.2
unnamed: P11.1, P11.10, R5.2
unnamed: P12.1, P12.10, R6.2
unnamed: P13.1, P13.10, R13.2
unnamed: P14.1, P14.10, R14.2
unnamed: Q1.2 (E), R1.1, R3.1
unnamed: Q2.2 (E), R2.1, R4.1
unnamed: Q3.2 (E), R5.1, R7.1
unnamed: Q4.2 (E), R6.1, R8.1
unnamed: Q5.2 (E), R13.1, R15.1
unnamed: Q6.2 (E), R14.1, R16.1

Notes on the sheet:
Holes
Shield for Arduino that uses the same pin disposition like "Uno" board Rev 3.
Switch Inputs/Bank Selectors
Switch Input Offset Selector Jumpers
